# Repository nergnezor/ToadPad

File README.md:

- Add https://adafruit.github.io/arduino-board-index/package_adafruit_index.json as an 'Additional Board Manager URL'
- Install Adafruit nRF52 board package 1.5.0
- Install Adafruit LED Backpack library 1.3.2

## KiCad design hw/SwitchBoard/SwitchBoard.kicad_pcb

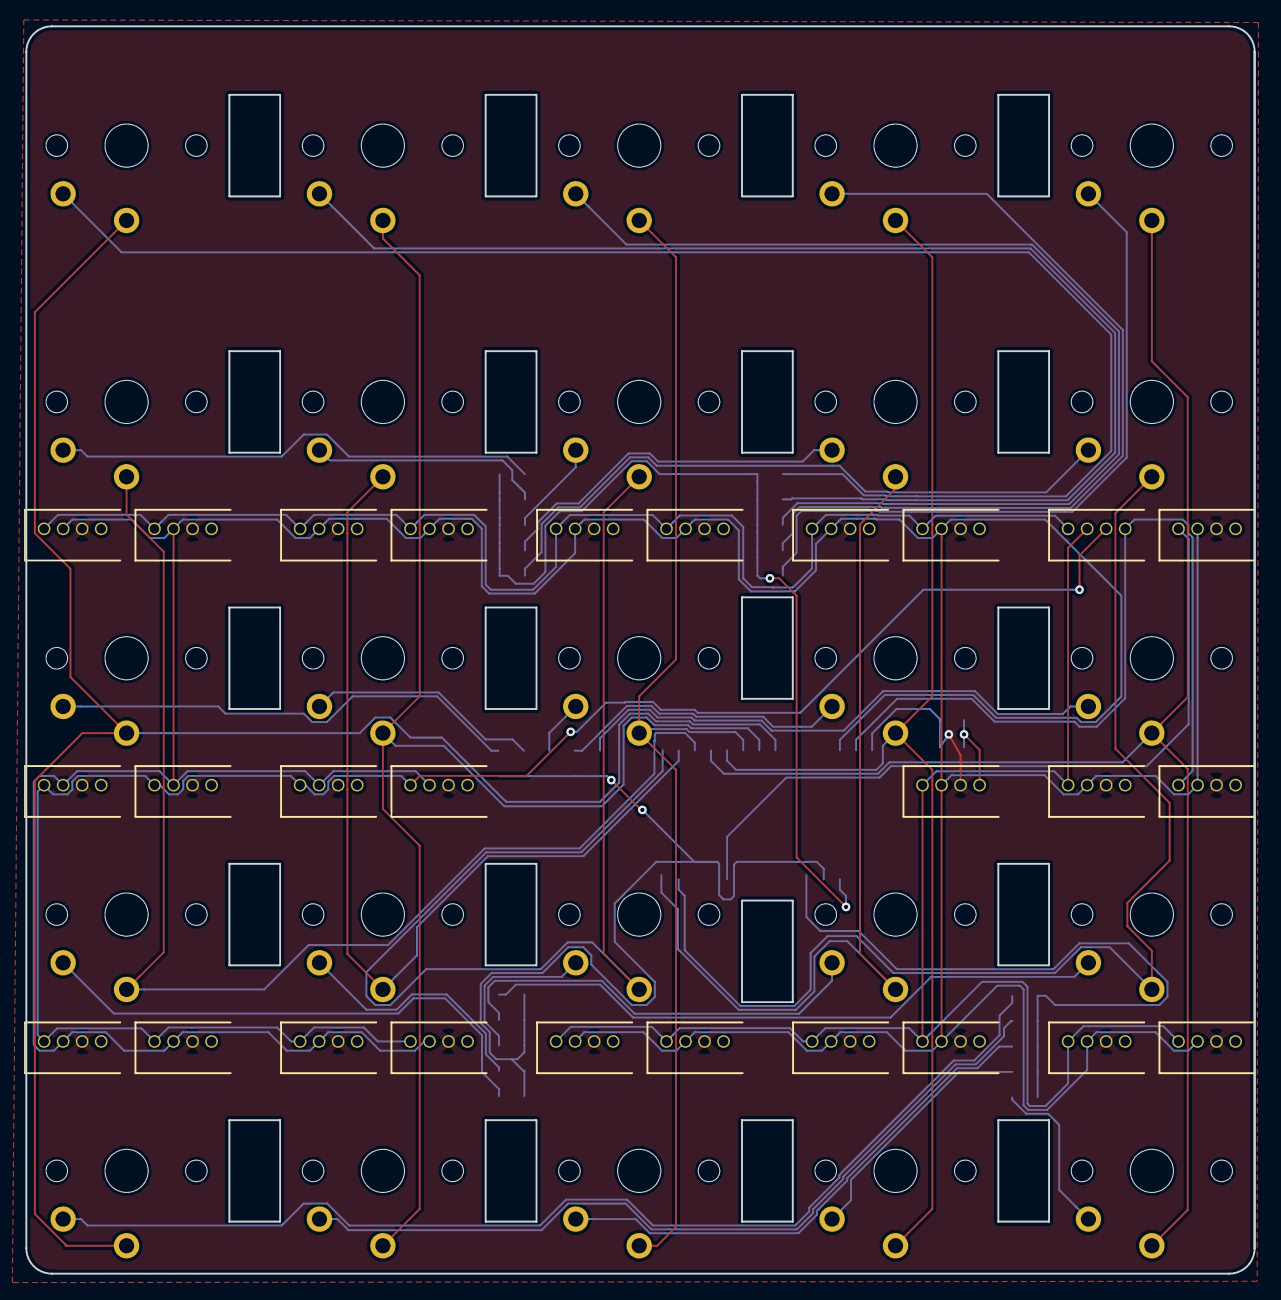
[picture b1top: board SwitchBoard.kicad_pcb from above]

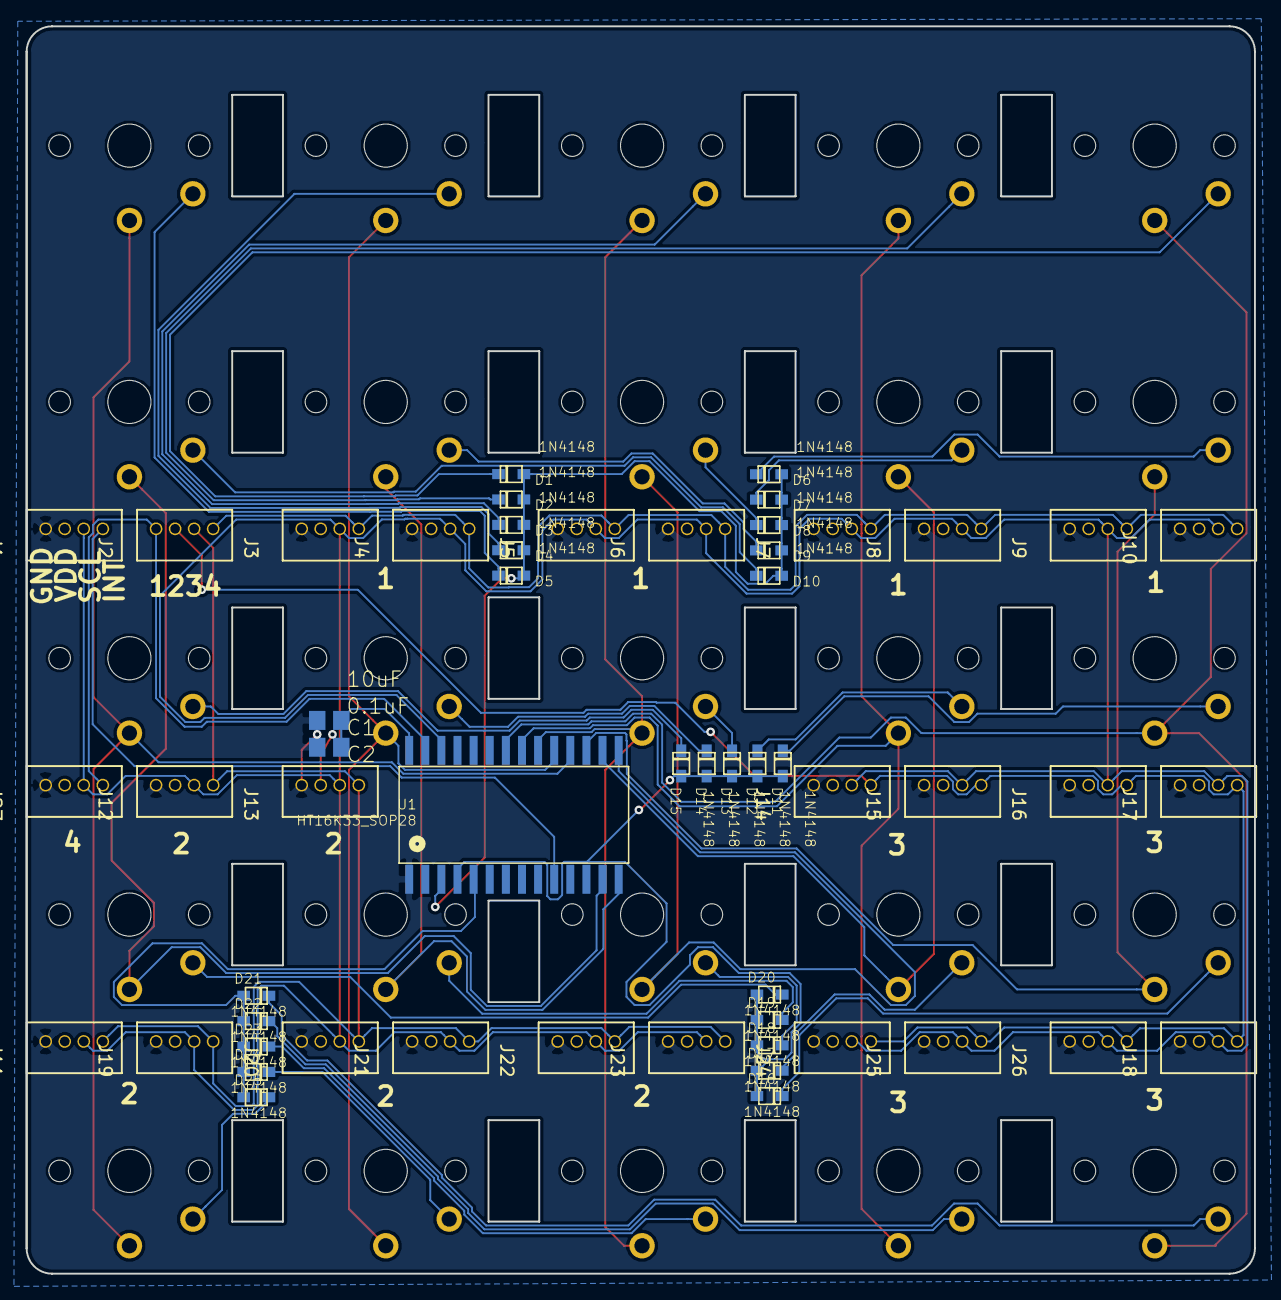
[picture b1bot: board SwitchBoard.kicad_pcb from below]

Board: 2 copper layers, 96.8 x 98.3 mm, 80 parts (55 on the bottom side), 46 nets.

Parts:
C1: 10uF; C0805
C2: 0.1uF; C0805
D1, D2, D3, D4, D5, D6, D7, D8, D9, D10, D11, D12, D13, D14, D15, D16, D17, D18, D19, D20, D21, D22, D23, D24, D25: 1N4148; SOD-323F
J1, J2, J3, J4, J5, J6, J7, J8, J9, J10, J11, J12, J13, J14, J15, J16, J17, J18, J19, J20, J21, J22, J23, J24, J25, J26, J27: Conn_01x04_Female; Grove_1x04
SW1, SW2, SW3, SW4, SW5, SW6, SW7, SW8, SW9, SW10, SW11, SW12, SW13, SW14, SW15, SW16, SW17, SW18, SW19, SW20, SW21, SW22, SW23, SW24, SW25: SW_Push; Kailh-PG1350-1u-No-Clickhole
U1: HT16K33_SOP28; SOP28_300MIL

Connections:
/GND: C1.2, C2.2, J1.1, J3.1, J4.1, J5.1, J6.1, J7.1, J8.1, J9.1, J10.1, J11.1, J12.1, J13.1, J14.1, J15.1, J16.1, J17.1, J18.1, J19.1, J20.1, J21.1, J22.1, J23.1, J24.1, J25.1, J26.1, J27.1, U1.P$1
/INT: J1.4, U1.P$10
/SCL: J1.3, J3.3, J4.3, J5.3, J6.3, J7.3, J8.3, J9.3, J10.3, J11.3, J12.3, J13.3, J14.3, J15.3, J16.3, J17.3, J18.3, J19.3, J20.3, J21.3, J22.3, J23.3, J24.3, J25.3, J26.3, J27.3, U1.P$26
/SDA1: J2.4, J3.4, J4.4, J5.4, J6.4, J7.4, J8.4, J9.4, J10.4
/SDA2: J2.3, J11.4, J12.4, J13.4, J19.4, J20.4, J21.4, J22.4, J23.4
/SDA3: J2.2, J14.4, J15.4, J16.4, J17.4, J18.4, J24.4, J25.4, J26.4
/SDA4: J2.1, J27.4, U1.P$27
/VDD: C1.1, C2.1, J1.2, J3.2, J4.2, J5.2, J6.2, J7.2, J8.2, J9.2, J10.2, J11.2, J12.2, J13.2, J14.2, J15.2, J16.2, J17.2, J18.2, J19.2, J20.2, J21.2, J22.2, J23.2, J24.2, J25.2, J26.2, J27.2, U1.P$28
unnamed: D1.A, D2.A, D3.A, D4.A, D5.A, D6.A, D7.A, D8.A, D9.A, D10.A, U1.P$3
unnamed: D1.C, SW1.2
unnamed: D2.C, SW2.2
unnamed: D3.C, SW3.2
unnamed: D4.C, SW4.2
unnamed: D5.C, SW5.2
unnamed: D6.C, SW6.2
unnamed: D7.C, SW7.2
unnamed: D8.C, SW8.2
unnamed: D9.C, SW9.2
unnamed: D10.C, SW10.2
unnamed: D11.A, D12.A, D13.A, D14.A, D15.A, D16.A, D17.A, D18.A, D19.A, D20.A, U1.P$4
unnamed: D11.C, SW11.2
unnamed: D12.C, SW12.2
unnamed: D13.C, SW13.2
unnamed: D14.C, SW14.2
unnamed: D15.C, SW15.2
unnamed: D16.C, SW16.2
unnamed: D17.C, SW17.2
unnamed: D18.C, SW18.2
unnamed: D19.C, SW19.2
unnamed: D20.C, SW20.2
unnamed: D21.A, D22.A, D23.A, D24.A, D25.A, U1.P$5
unnamed: D21.C, SW21.2
unnamed: D22.C, SW22.2
unnamed: D23.C, SW23.2
unnamed: D24.C, SW24.2
unnamed: D25.C, SW25.2
unnamed: SW1.1, SW11.1, SW21.1, U1.P$22
unnamed: SW10.1, SW20.1, U1.P$13
unnamed: SW2.1, SW12.1, SW22.1, U1.P$21
unnamed: SW3.1, SW13.1, SW23.1, U1.P$20
unnamed: SW4.1, SW14.1, SW24.1, U1.P$19
unnamed: SW5.1, SW15.1, SW25.1, U1.P$18
unnamed: SW6.1, SW16.1, U1.P$17
unnamed: SW7.1, SW17.1, U1.P$16
unnamed: SW8.1, SW18.1, U1.P$15
unnamed: SW9.1, SW19.1, U1.P$14

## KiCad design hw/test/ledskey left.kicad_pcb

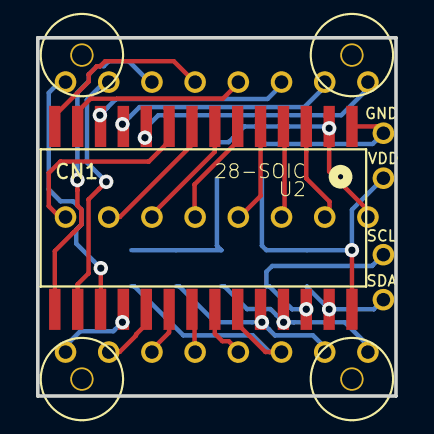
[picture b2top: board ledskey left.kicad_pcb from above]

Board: 2 copper layers, 19.9 x 19.9 mm, 10 parts (0 on the bottom side), 29 nets.

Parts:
C1: 10uF; C0805
CN1: 1X4-CLEANBIG; 1X04-CLEANBIG
D1: 1N4148; SOD-323F
LED2: DISP_SEGMENT_8X8_BICOLOR_ROWCATHODEMI2A883XX; BL-M07A881
R1, R2, R3, R4, R5: 10K; R0805
U2: 28-SOIC; SOP28_300MIL

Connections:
/A0: LED2.6, R4.2, U2.P$23
/A1: LED2.7, R3.2, U2.P$24
/A2: LED2.8, R5.2, U2.P$25
/SCL: CN1.2, R1.2, U2.P$26
/SDA: CN1.1, R2.2, U2.P$27
GND: C1.2, CN1.4, U2.P$1
unnamed: D1.A, LED2.16, U2.P$2
unnamed: D1.C, R3.1, R4.1, R5.1
unnamed: LED2.1, U2.P$18
unnamed: LED2.2, U2.P$19
unnamed: LED2.3, U2.P$20
unnamed: LED2.4, U2.P$21
unnamed: LED2.5, U2.P$22
unnamed: LED2.9, U2.P$9
unnamed: LED2.10, U2.P$8
unnamed: LED2.11, U2.P$7
unnamed: LED2.12, U2.P$6
unnamed: LED2.13, U2.P$5
unnamed: LED2.14, U2.P$4
unnamed: LED2.15, U2.P$3
unnamed: LED2.17, U2.P$17
unnamed: LED2.18, U2.P$16
unnamed: LED2.19, U2.P$15
unnamed: LED2.20, U2.P$14
unnamed: LED2.21, U2.P$13
unnamed: LED2.22, U2.P$12
unnamed: LED2.23, U2.P$11
unnamed: LED2.24, U2.P$10
VDD: C1.1, CN1.3, R1.1, R2.1, U2.P$28

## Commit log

2018-04-30 initial
2018-05-03 788ahg image
2018-05-03 added kicad files
2018-05-04 lots of files
2018-05-04 changed schema to help routing
2018-05-07 added address resistors to pcb layout
2018-05-08 finished layout except connector
2018-06-18 ordered pcb!
2018-07-09 added bicolor matrix 8x8 Arduino code
2018-10-05 added real matrix
2018-10-05 2.4 pitch
2018-11-27 added 3d
2018-11-29 shipped 3D!
2018-12-09 added esp32 ble code
2018-12-10 started switchboard
2018-12-11 finished button matrix
2018-12-17 pcb switch matrix + ball ani
2018-12-17 almost routed switchboard
2018-12-18 finished switch routing. missing i2c
2018-12-18 fixed pad errors
2018-12-18 added connector footprint
2018-12-18 ignore
2019-01-06 added holes for cables
2019-01-06 final key switch matrix prune
2019-01-08 schematic done. layout needs cleanup
2019-01-08 almost done with routing
2019-01-09 ready to order?
2019-01-09 refined
2019-01-09 ordered switchboard aka Komando 0.1
2019-01-10 post oshpark send CLK fixes
2019-03-06 auto find
2019-03-14 triple I2C working on Feather NRF52
2019-03-14 Auto enumerate all keys
2019-03-15 key scan almost working
2019-03-16 Keys work perfectly!
2019-03-21 fonts
2023-07-02 only keyscan
2023-07-03 display works again, but no keyscan now. LED Backpack v1.1.10
2023-07-03 All working
2023-07-03 Override drawing to align colors
2023-07-03 fix rotation
2023-07-03 smile
2023-07-03 int readKeys(), not working
2023-07-04 still not
2023-07-04 works. was hw usb hub issue
2023-07-04 cleanup
2023-07-04 display file
2023-07-04 extract display
2023-07-04 extract init, not working yet
2023-07-04 Serial.println(Wire.availableForWrite());
2023-07-04 print .
2023-07-04 use vector
2023-07-04 mapping
2023-07-04 almost
2023-07-05 fix display_order
2023-07-05 display and key location index done!
2023-07-05 Draw shadowed
2023-07-06 move init to display
2023-07-06 refac
2023-07-06 display config
2023-07-06 max fullscreen refresh
2023-07-06 clang format (Visual studio -> Google)
2023-07-06 fix build
2023-07-06 remove brackets
2023-07-06 multitouch. hangs after a while
2023-07-07 print
2023-07-07 cleanup. still no A
2023-07-07 rects
2023-07-08 Draw multi display rect
2023-07-08 animation and press. works a few presses
2023-07-08 animate big rect
2023-07-08 Install instructions
2023-07-09 only draw changed [RTOS ] Task loop: failed to Malloc
2023-07-09 static pixels
2023-07-11 empty pixels again
2023-07-11 Clear previous changed
2023-07-14 Draw::init
2023-07-14 start draw
2023-07-15 animate line
2023-07-15 rgb init
2023-07-15 faster swirl
2023-07-17 full screen image!
2023-07-17 rotate vertical. something fishy
2023-07-23 ble uart
2023-07-25 start/stop on android uart send
2023-09-01 nerg
2024-11-02 add rust hello world
2024-11-02 add ht16k33
2024-11-03 led blink
2024-11-04 add rust esp with std lib
